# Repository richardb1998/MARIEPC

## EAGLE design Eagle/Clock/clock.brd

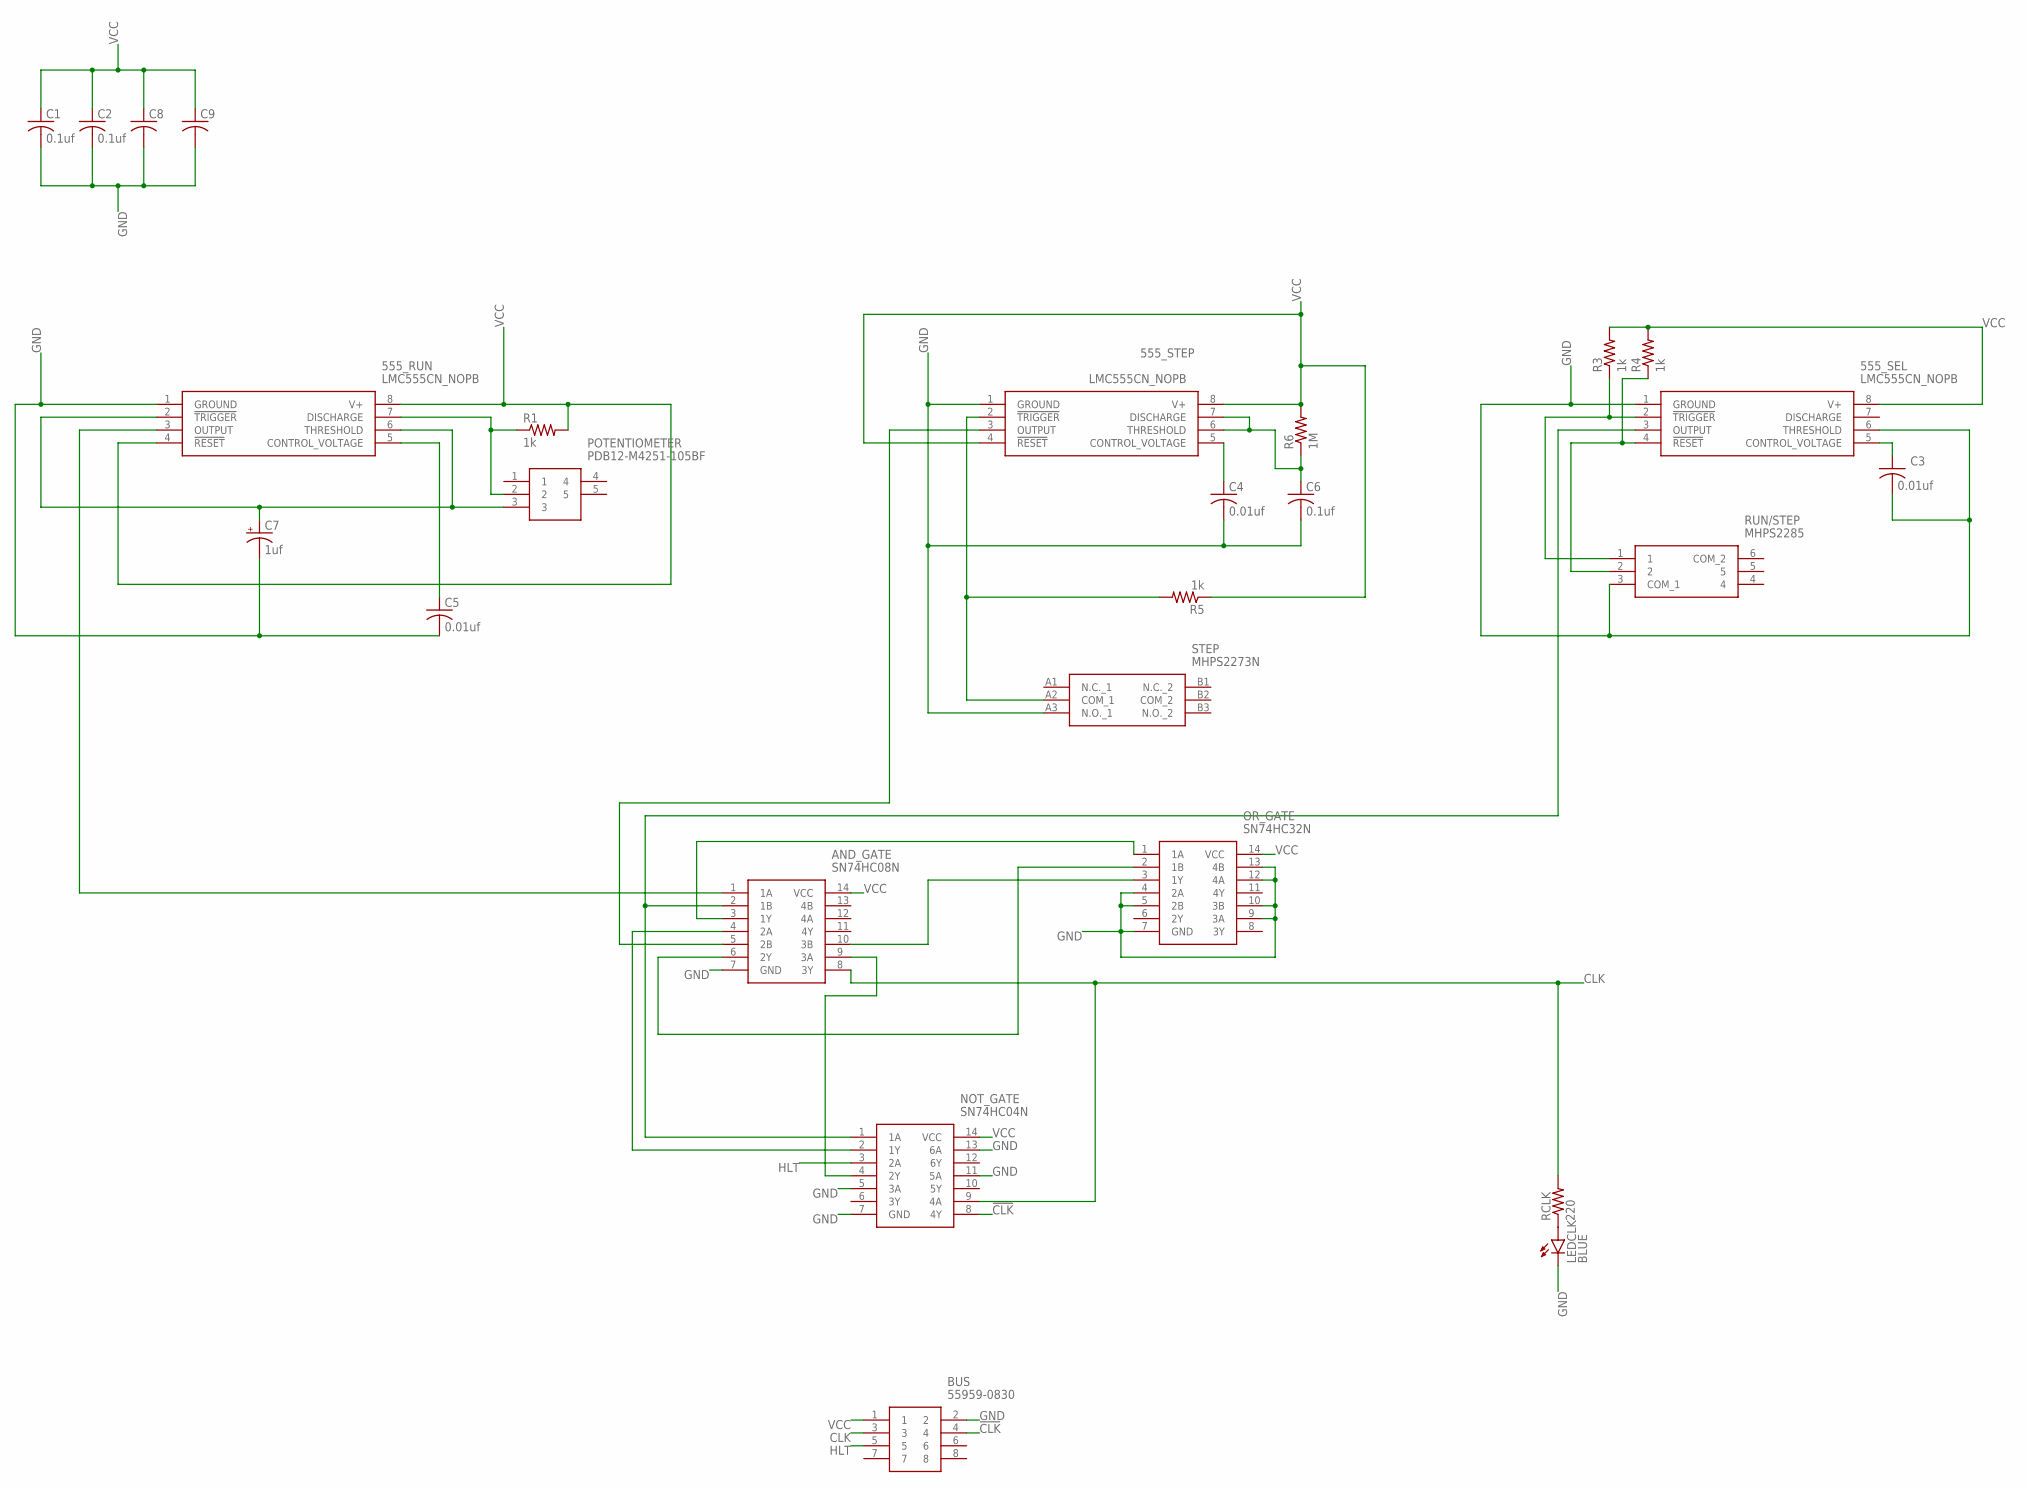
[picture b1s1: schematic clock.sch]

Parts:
555_RUN, 555_SEL, 555_STEP: LMC555CN_NOPB; DIP794W53P254L959H508Q8N
AND_GATE: SN74HC08N; DIP794W53P254L1930H508Q14N
BUS: 55959-0830; SHDR8W65P250X200_2X4_1140X1400
C1, C2, C6: 0.1uf; C025-024X044
C3, C4, C5: 0.01uf; C025-024X044
C7: 1uf; E5-5
C8, C9: C-US025-024X044; C025-024X044
LEDCLK: BLUE; LED3MM
NOT_GATE: SN74HC04N; DIP794W53P254L1930H508Q14N
OR_GATE: SN74HC32N; DIP794W53P254L1930H508Q14N
POTENTIOMETER: PDB12-M4251-105BF; PDB12M4251105BF
R1, R3, R4, R5: 1k; 0204/7
R6: 1M; 0204/7
RCLK: 220; 0204/7
RUN/STEP: MHPS2285
STEP: MHPS2273N

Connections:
!CLK: BUS.4, NOT_GATE.8 (4Y)
CLK: AND_GATE.8 (3Y), BUS.3, NOT_GATE.9 (4A), RCLK.2
GND: 555_RUN.1 (GROUND), 555_SEL.1 (GROUND), 555_SEL.6 (THRESHOLD), 555_STEP.1 (GROUND), AND_GATE.7 (GND), BUS.2, C1.2, C2.2, C3.2, C4.2, C5.2, C6.2, C7.-, C8.2, C9.2, LEDCLK.K (C), NOT_GATE.5 (3A), NOT_GATE.7 (GND), NOT_GATE.11 (5A), NOT_GATE.13 (6A), OR_GATE.4 (2A), OR_GATE.5 (2B), OR_GATE.7 (GND), OR_GATE.9 (3A), OR_GATE.10 (3B), OR_GATE.12 (4A), OR_GATE.13 (4B), RUN/STEP.3 (COM_1), STEP.A3 (N.O._1)
HLT: BUS.5, NOT_GATE.3 (2A)
unnamed: 555_RUN.7 (DISCHARGE), POTENTIOMETER.2, R1.1
unnamed: 555_RUN.5 (CONTROL_VOLTAGE), C5.1
unnamed: 555_RUN.3 (OUTPUT), AND_GATE.1 (1A)
unnamed: 555_STEP.6 (THRESHOLD), 555_STEP.7 (DISCHARGE), C6.1, R6.1
unnamed: 555_STEP.5 (CONTROL_VOLTAGE), C4.1
unnamed: 555_STEP.3 (OUTPUT), AND_GATE.5 (2B)
unnamed: 555_STEP.2 (!TRIGGER), R5.2, STEP.A2 (COM_1)
unnamed: 555_SEL.2 (!TRIGGER), R3.1, RUN/STEP.1
unnamed: 555_SEL.4 (!RESET), R4.1, RUN/STEP.2
unnamed: 555_SEL.3 (OUTPUT), AND_GATE.2 (1B), NOT_GATE.1 (1A)
unnamed: 555_SEL.5 (CONTROL_VOLTAGE), C3.1
unnamed: LEDCLK.A, RCLK.1
unnamed: AND_GATE.4 (2A), NOT_GATE.2 (1Y)
unnamed: AND_GATE.3 (1Y), OR_GATE.1 (1A)
unnamed: AND_GATE.9 (3A), NOT_GATE.4 (2Y)
unnamed: AND_GATE.6 (2Y), OR_GATE.2 (1B)
unnamed: AND_GATE.10 (3B), OR_GATE.3 (1Y)
POTENTIOMETER: 555_RUN.2 (!TRIGGER), 555_RUN.6 (THRESHOLD), C7.+, POTENTIOMETER.3
VCC: 555_RUN.4 (!RESET), 555_RUN.8 (V+), 555_SEL.8 (V+), 555_STEP.4 (!RESET), 555_STEP.8 (V+), AND_GATE.14 (VCC), BUS.1, C1.1, C2.1, C8.1, C9.1, NOT_GATE.14 (VCC), OR_GATE.14 (VCC), R1.2, R3.2, R4.2, R5.1, R6.2

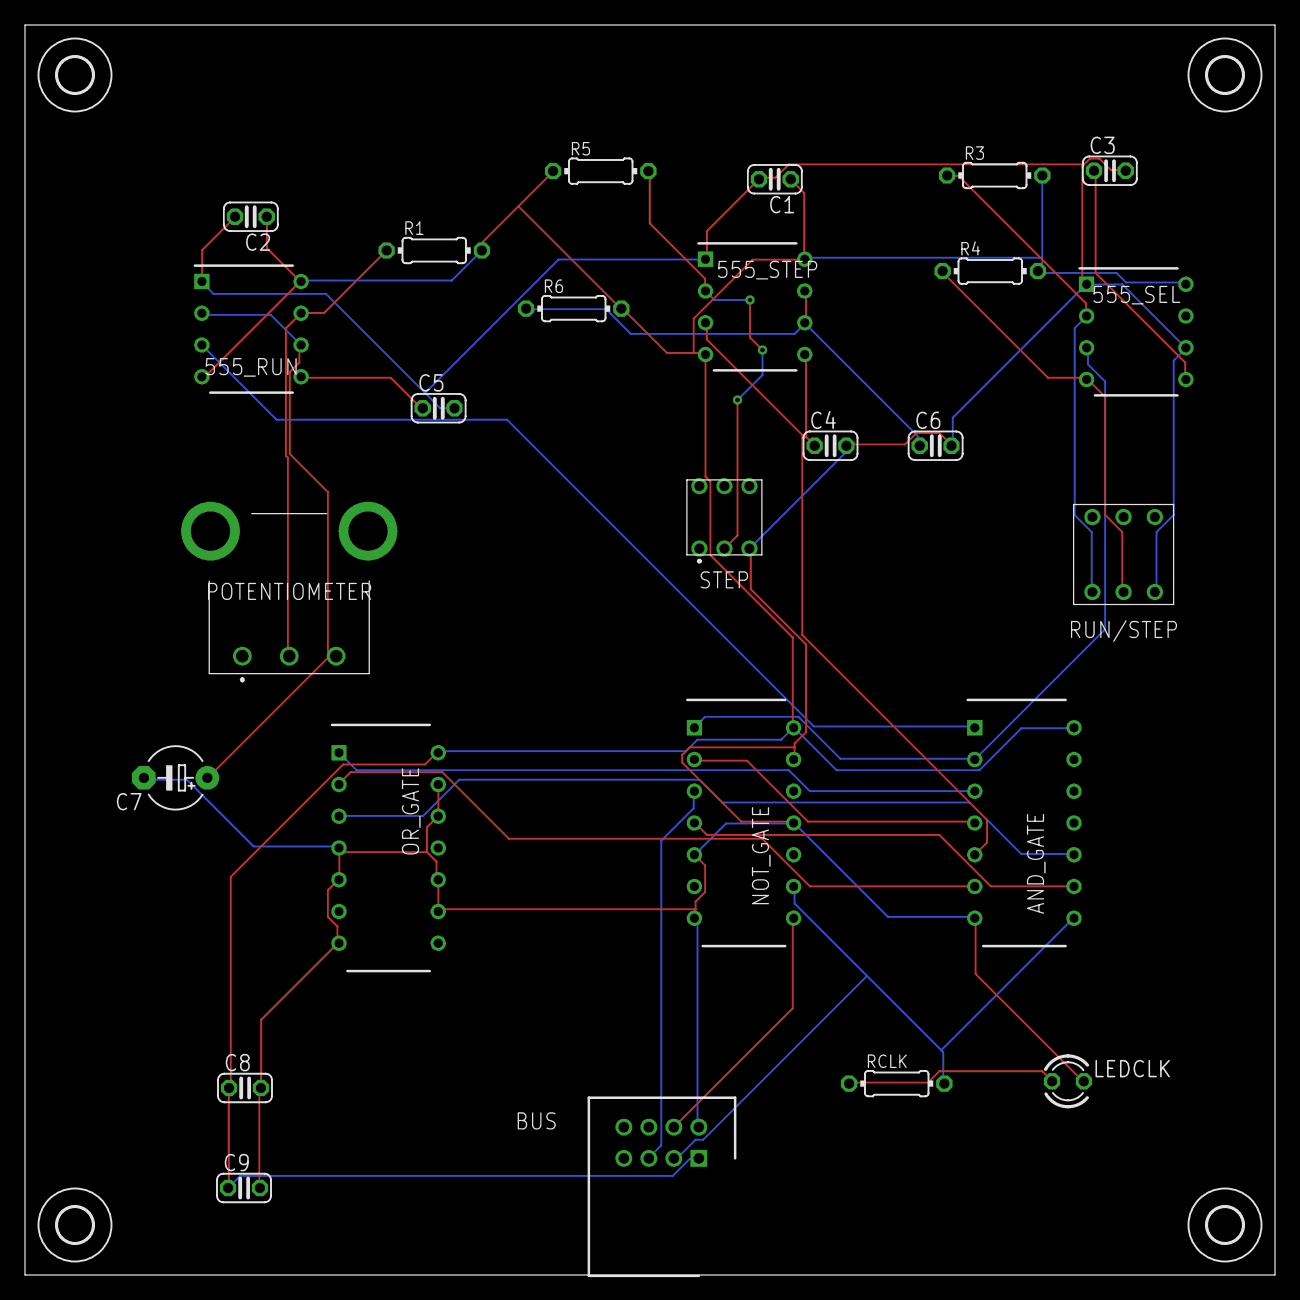
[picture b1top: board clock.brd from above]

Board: 2 copper layers, 100.0 x 100.0 mm, 30 parts (0 on the bottom side), 23 nets.

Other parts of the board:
U$1, U$2, U$3, U$4: 2,8

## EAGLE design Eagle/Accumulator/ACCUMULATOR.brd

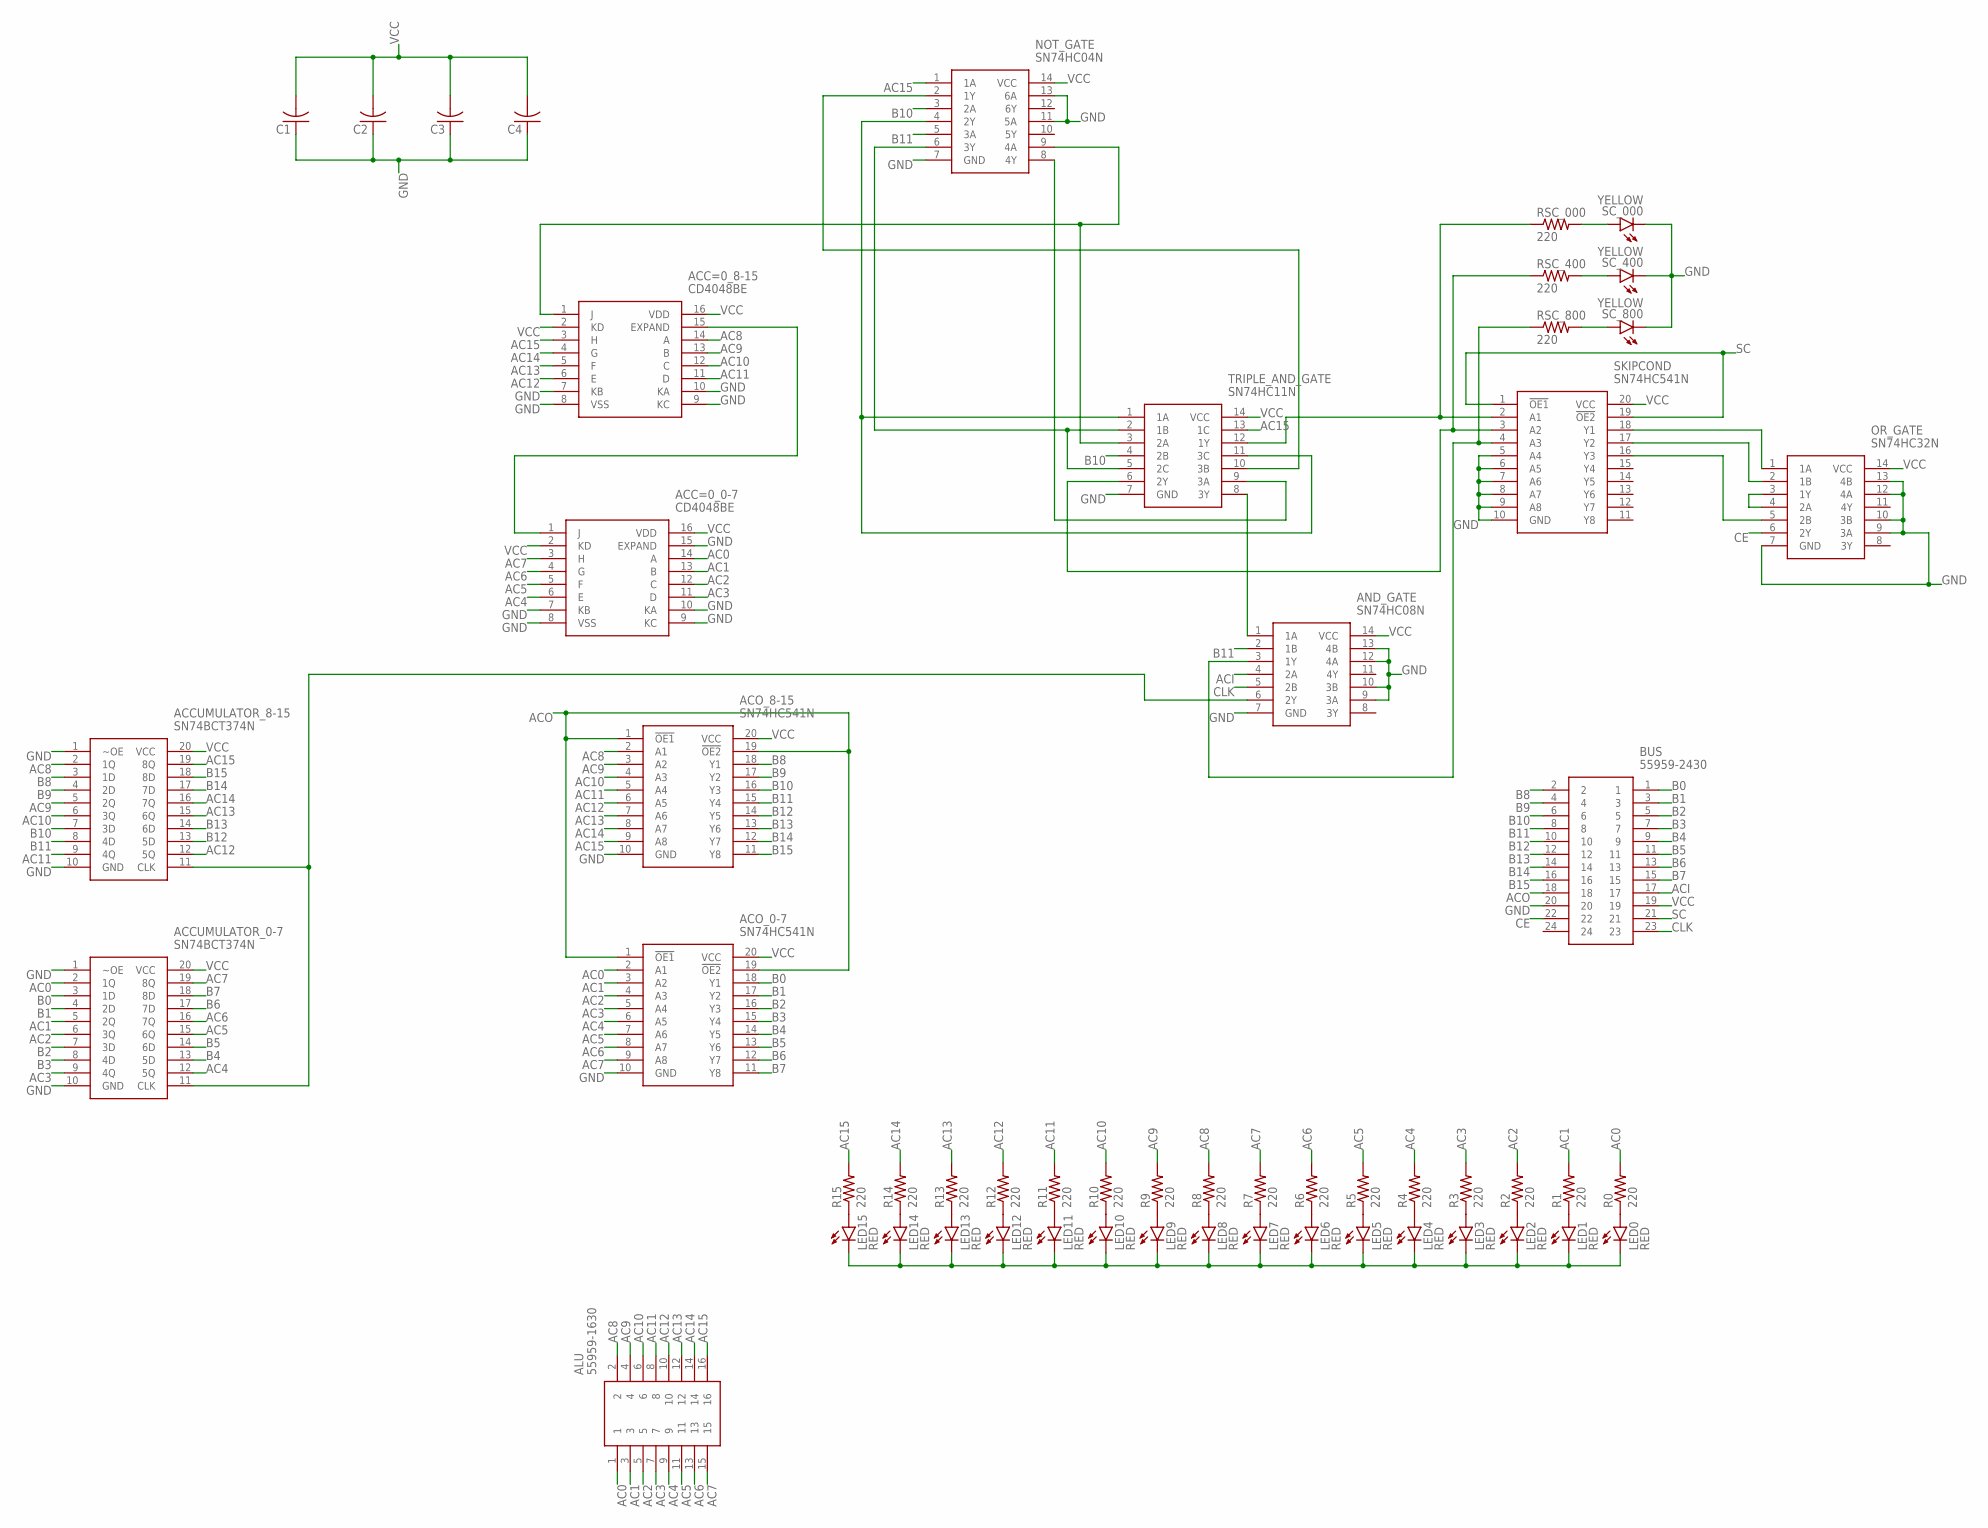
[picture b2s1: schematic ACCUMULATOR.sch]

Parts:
ACC=0_0-7, ACC=0_8-15: CD4048BE; DIP254P762X508-16
ACCUMULATOR_0-7, ACCUMULATOR_8-15: SN74BCT374N; DIP254P762X508-20
ACO_0-7, ACO_8-15: SN74HC541N; DIP794W53P254L2540H508Q20N
ALU: 55959-1630; SHDR16W65P250X200_2X8_1940X140
AND_GATE: SN74HC08N; DIP794W53P254L1930H508Q14N
BUS: 55959-2430; 559592430
C1, C2, C3, C4: C-US025-024X044; C025-024X044
LED0, LED1, LED2, LED3, LED4, LED5, LED6, LED7, LED8, LED9, LED10, LED11, LED12, LED13, LED14, LED15: RED; LED3MM
NOT_GATE: SN74HC04N; DIP794W53P254L1930H508Q14N
OR_GATE: SN74HC32N; DIP794W53P254L1930H508Q14N
R0, R1, R2, R3, R4, R5, R6, R7, R8, R9, R10, R11, R12, R13, R14, R15: 220; 0204/7
RSC_000, RSC_400, RSC_800: 220; 0204/7
SC_000, SC_400, SC_800: YELLOW; LED3MM
SKIPCOND: SN74HC541N; DIP794W53P254L2540H508Q20N
TRIPLE_AND_GATE: SN74HC11N; DIP794W53P254L1930H508Q14N

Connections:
AC0: ACC=0_0-7.14 (A), ACCUMULATOR_0-7.2 (1Q), ACO_0-7.2 (A1), ALU.1, R0.2
AC1: ACC=0_0-7.13 (B), ACCUMULATOR_0-7.5 (2Q), ACO_0-7.3 (A2), ALU.3, R1.2
AC2: ACC=0_0-7.12 (C), ACCUMULATOR_0-7.6 (3Q), ACO_0-7.4 (A3), ALU.5, R2.2
AC3: ACC=0_0-7.11 (D), ACCUMULATOR_0-7.9 (4Q), ACO_0-7.5 (A4), ALU.7, R3.2
AC4: ACC=0_0-7.6 (E), ACCUMULATOR_0-7.12 (5Q), ACO_0-7.6 (A5), ALU.9, R4.2
AC5: ACC=0_0-7.5 (F), ACCUMULATOR_0-7.15 (6Q), ACO_0-7.7 (A6), ALU.11, R5.2
AC6: ACC=0_0-7.4 (G), ACCUMULATOR_0-7.16 (7Q), ACO_0-7.8 (A7), ALU.13, R6.2
AC7: ACC=0_0-7.3 (H), ACCUMULATOR_0-7.19 (8Q), ACO_0-7.9 (A8), ALU.15, R7.2
AC8: ACC=0_8-15.14 (A), ACCUMULATOR_8-15.2 (1Q), ACO_8-15.2 (A1), ALU.2, R8.2
AC9: ACC=0_8-15.13 (B), ACCUMULATOR_8-15.5 (2Q), ACO_8-15.3 (A2), ALU.4, R9.2
AC10: ACC=0_8-15.12 (C), ACCUMULATOR_8-15.6 (3Q), ACO_8-15.4 (A3), ALU.6, R10.2
AC11: ACC=0_8-15.11 (D), ACCUMULATOR_8-15.9 (4Q), ACO_8-15.5 (A4), ALU.8, R11.2
AC12: ACC=0_8-15.6 (E), ACCUMULATOR_8-15.12 (5Q), ACO_8-15.6 (A5), ALU.10, R12.2
AC13: ACC=0_8-15.5 (F), ACCUMULATOR_8-15.15 (6Q), ACO_8-15.7 (A6), ALU.12, R13.2
AC14: ACC=0_8-15.4 (G), ACCUMULATOR_8-15.16 (7Q), ACO_8-15.8 (A7), ALU.14, R14.2
AC15: ACC=0_8-15.3 (H), ACCUMULATOR_8-15.19 (8Q), ACO_8-15.9 (A8), ALU.16, NOT_GATE.1 (1A), R15.2, TRIPLE_AND_GATE.13 (1C)
ACI: AND_GATE.4 (2A), BUS.17
ACO: ACO_0-7.1 (!OE1), ACO_0-7.19 (!OE2), ACO_8-15.1 (!OE1), ACO_8-15.19 (!OE2), BUS.18
B0: ACCUMULATOR_0-7.3 (1D), ACO_0-7.18 (Y1), BUS.1
B1: ACCUMULATOR_0-7.4 (2D), ACO_0-7.17 (Y2), BUS.3
B2: ACCUMULATOR_0-7.7 (3D), ACO_0-7.16 (Y3), BUS.5
B3: ACCUMULATOR_0-7.8 (4D), ACO_0-7.15 (Y4), BUS.7
B4: ACCUMULATOR_0-7.13 (5D), ACO_0-7.14 (Y5), BUS.9
B5: ACCUMULATOR_0-7.14 (6D), ACO_0-7.13 (Y6), BUS.11
B6: ACCUMULATOR_0-7.17 (7D), ACO_0-7.12 (Y7), BUS.13
B7: ACCUMULATOR_0-7.18 (8D), ACO_0-7.11 (Y8), BUS.15
B8: ACCUMULATOR_8-15.3 (1D), ACO_8-15.18 (Y1), BUS.2
B9: ACCUMULATOR_8-15.4 (2D), ACO_8-15.17 (Y2), BUS.4
B10: ACCUMULATOR_8-15.7 (3D), ACO_8-15.16 (Y3), BUS.6, NOT_GATE.3 (2A), TRIPLE_AND_GATE.4 (2B)
B11: ACCUMULATOR_8-15.8 (4D), ACO_8-15.15 (Y4), AND_GATE.2 (1B), BUS.8, NOT_GATE.5 (3A)
B12: ACCUMULATOR_8-15.13 (5D), ACO_8-15.14 (Y5), BUS.10
B13: ACCUMULATOR_8-15.14 (6D), ACO_8-15.13 (Y6), BUS.12
B14: ACCUMULATOR_8-15.17 (7D), ACO_8-15.12 (Y7), BUS.14
B15: ACCUMULATOR_8-15.18 (8D), ACO_8-15.11 (Y8), BUS.16
CE: BUS.22, OR_GATE.6 (2Y)
CLK: AND_GATE.5 (2B), BUS.23
GND: ACC=0_0-7.7 (KB), ACC=0_0-7.8 (VSS), ACC=0_0-7.9 (KC), ACC=0_0-7.10 (KA), ACC=0_0-7.15 (EXPAND), ACC=0_8-15.7 (KB), ACC=0_8-15.8 (VSS), ACC=0_8-15.9 (KC), ACC=0_8-15.10 (KA), ACCUMULATOR_0-7.1 (~OE), ACCUMULATOR_0-7.10 (GND), ACCUMULATOR_8-15.1 (~OE), ACCUMULATOR_8-15.10 (GND), ACO_0-7.10 (GND), ACO_8-15.10 (GND), AND_GATE.7 (GND), AND_GATE.9 (3A), AND_GATE.10 (3B), AND_GATE.12 (4A), AND_GATE.13 (4B), BUS.20, C1.1, C2.1, C3.1, C4.1, NOT_GATE.7 (GND), NOT_GATE.11 (5A), NOT_GATE.13 (6A), OR_GATE.7 (GND), OR_GATE.9 (3A), OR_GATE.10 (3B), OR_GATE.12 (4A), OR_GATE.13 (4B), SC_000.K (C), SC_400.K (C), SC_800.K (C), SKIPCOND.5 (A4), SKIPCOND.6 (A5), SKIPCOND.7 (A6), SKIPCOND.8 (A7), SKIPCOND.9 (A8), SKIPCOND.10 (GND), TRIPLE_AND_GATE.7 (GND)
unnamed: ACC=0_0-7.1 (J), ACC=0_8-15.15 (EXPAND)
unnamed: RSC_800.2, SC_800.A
unnamed: RSC_400.2, SC_400.A
unnamed: NOT_GATE.4 (2Y), TRIPLE_AND_GATE.1 (1A), TRIPLE_AND_GATE.11 (3C)
unnamed: ACCUMULATOR_0-7.11 (CLK), ACCUMULATOR_8-15.11 (CLK), AND_GATE.6 (2Y)
unnamed: ACC=0_8-15.1 (J), NOT_GATE.9 (4A), TRIPLE_AND_GATE.3 (2A)
unnamed: NOT_GATE.6 (3Y), TRIPLE_AND_GATE.2 (1B), TRIPLE_AND_GATE.5 (2C)
unnamed: RSC_400.1, SKIPCOND.3 (A2), TRIPLE_AND_GATE.6 (2Y)
unnamed: RSC_000.1, SKIPCOND.2 (A1), TRIPLE_AND_GATE.12 (1Y)
unnamed: RSC_000.2, SC_000.A
unnamed: LED0.K (C), LED1.K (C), LED2.K (C), LED3.K (C), LED4.K (C), LED5.K (C), LED6.K (C), LED7.K (C), LED8.K (C), LED9.K (C), LED10.K (C), LED11.K (C), LED12.K (C), LED13.K (C), LED14.K (C), LED15.K (C)
unnamed: NOT_GATE.8 (4Y), TRIPLE_AND_GATE.9 (3A)
unnamed: NOT_GATE.2 (1Y), TRIPLE_AND_GATE.10 (3B)
unnamed: LED1.A, R1.1
unnamed: AND_GATE.1 (1A), TRIPLE_AND_GATE.8 (3Y)
unnamed: LED2.A, R2.1
unnamed: AND_GATE.3 (1Y), RSC_800.1, SKIPCOND.4 (A3)
unnamed: LED3.A, R3.1
unnamed: LED4.A, R4.1
unnamed: LED5.A, R5.1
unnamed: LED6.A, R6.1
unnamed: LED7.A, R7.1
unnamed: LED8.A, R8.1
unnamed: LED9.A, R9.1
unnamed: LED10.A, R10.1
unnamed: LED11.A, R11.1
unnamed: LED12.A, R12.1
unnamed: LED13.A, R13.1
unnamed: LED14.A, R14.1
unnamed: LED15.A, R15.1
unnamed: LED0.A, R0.1
unnamed: OR_GATE.1 (1A), SKIPCOND.18 (Y1)
unnamed: OR_GATE.2 (1B), SKIPCOND.17 (Y2)
unnamed: OR_GATE.3 (1Y), OR_GATE.4 (2A)
unnamed: OR_GATE.5 (2B), SKIPCOND.16 (Y3)
SC: BUS.21, SKIPCOND.1 (!OE1), SKIPCOND.19 (!OE2)
VCC: ACC=0_0-7.2 (KD), ACC=0_0-7.16 (VDD), ACC=0_8-15.2 (KD), ACC=0_8-15.16 (VDD), ACCUMULATOR_0-7.20 (VCC), ACCUMULATOR_8-15.20 (VCC), ACO_0-7.20 (VCC), ACO_8-15.20 (VCC), AND_GATE.14 (VCC), BUS.19, C1.2, C2.2, C3.2, C4.2, NOT_GATE.14 (VCC), OR_GATE.14 (VCC), SKIPCOND.20 (VCC), TRIPLE_AND_GATE.14 (VCC)

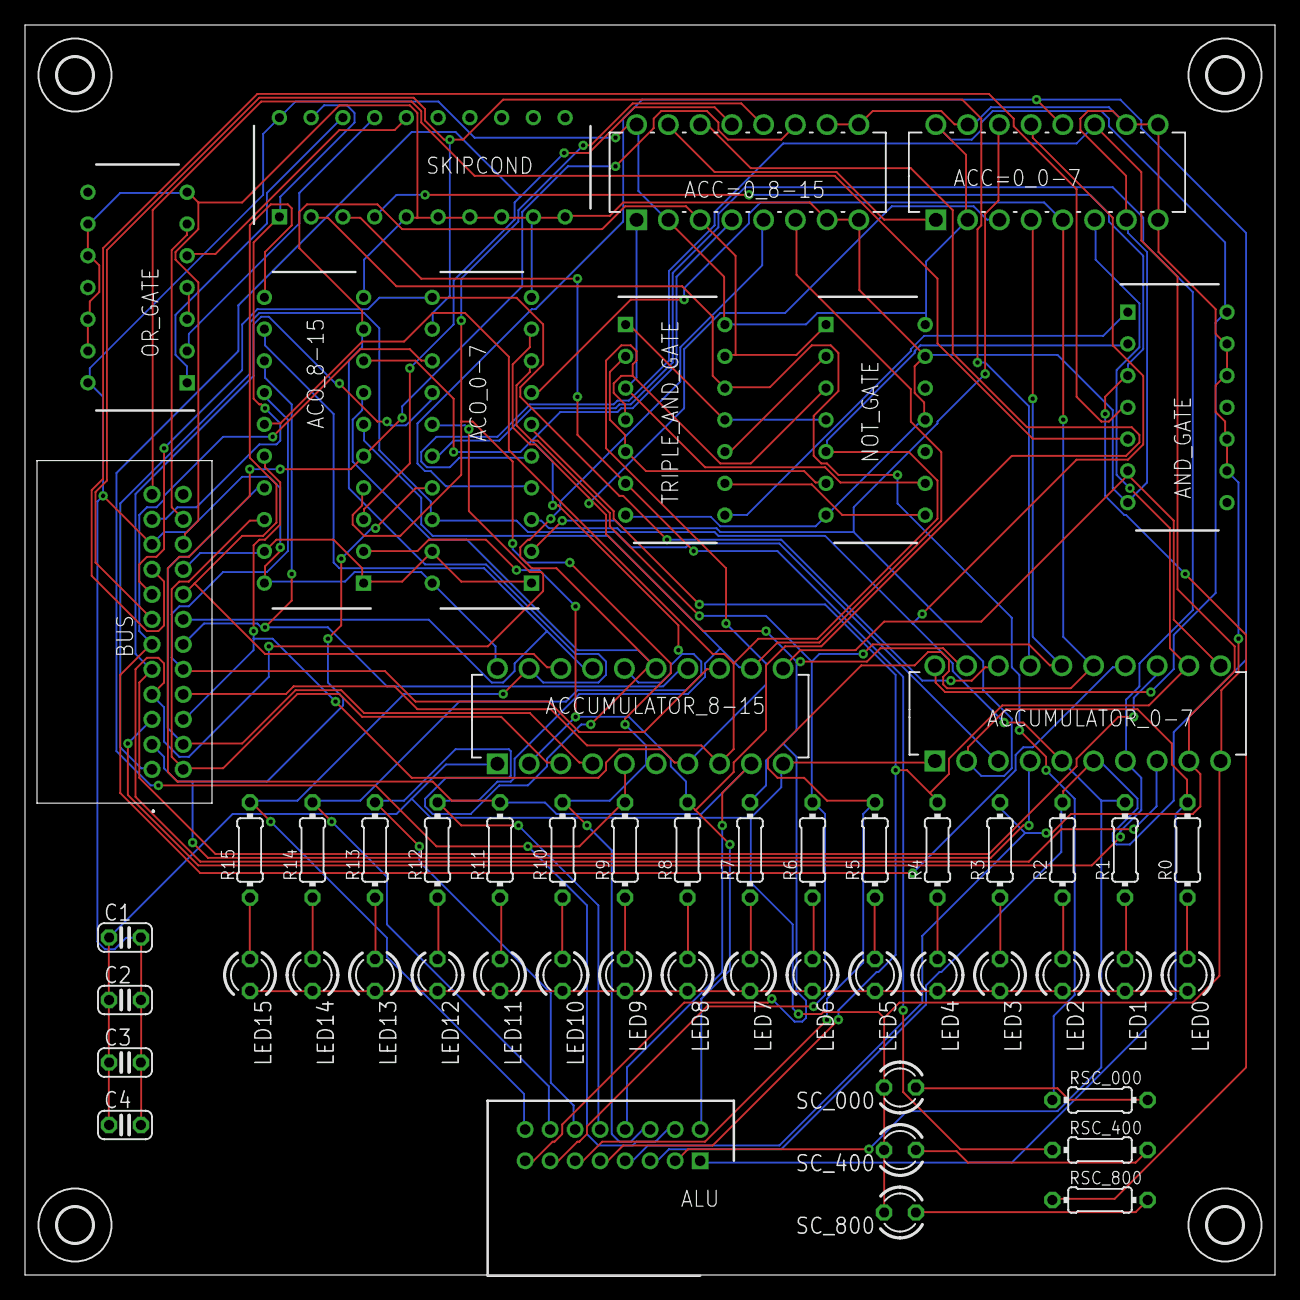
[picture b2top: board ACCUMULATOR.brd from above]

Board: 2 copper layers, 100.0 x 100.0 mm, 59 parts (0 on the bottom side), 74 nets.

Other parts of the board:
U$1, U$2, U$3, U$4: 2,8
